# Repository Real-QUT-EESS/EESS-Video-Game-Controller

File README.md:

# EESS-Video-Game-Controller
A repository for the video game controller project from EESS

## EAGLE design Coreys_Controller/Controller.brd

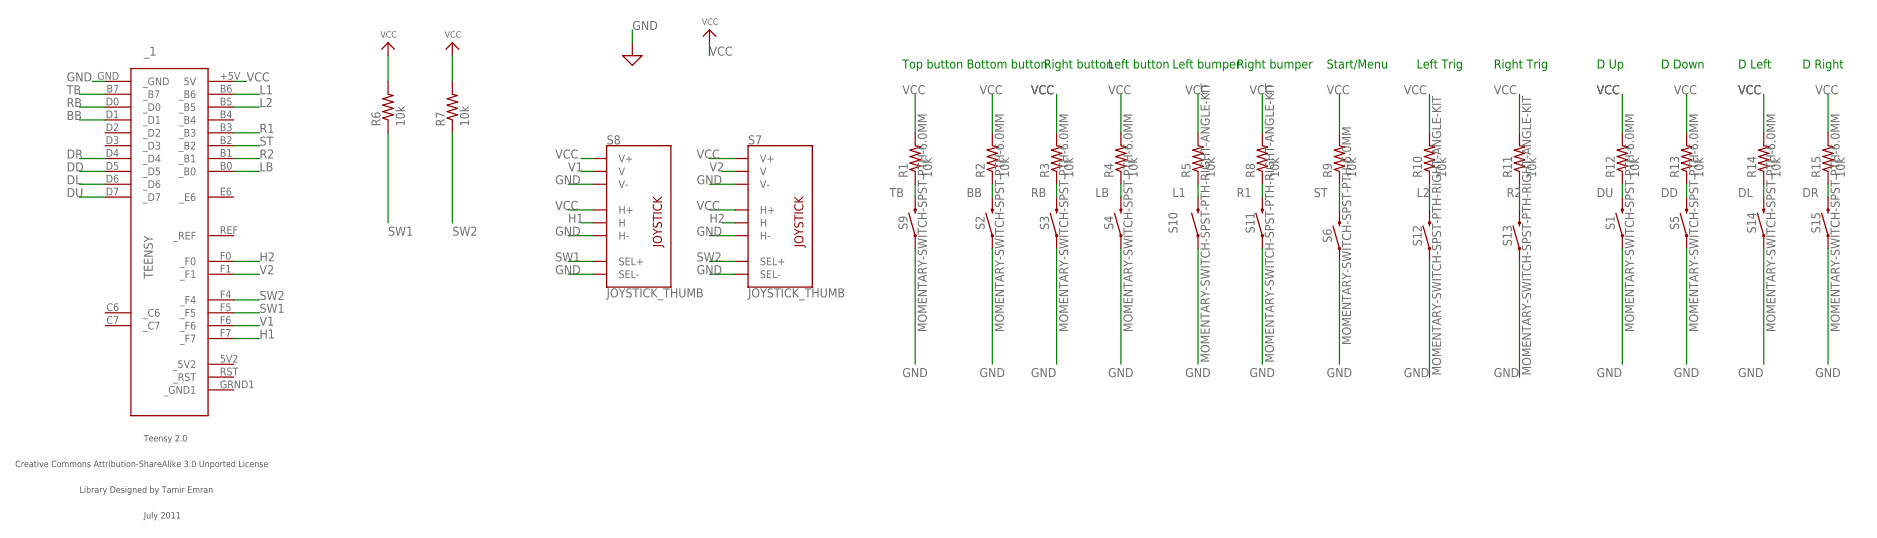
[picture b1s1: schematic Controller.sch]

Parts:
R1, R2, R3, R4, R5, R6, R7, R8, R9, R10, R11, R12, R13, R14, R15: 10k; 0207/10
S1, S2, S3, S4, S5, S6, S9, S14, S15: MOMENTARY-SWITCH-SPST-PTH-6.0MM; TACTILE_SWITCH_PTH_6.0MM
S7, S8: JOYSTICK_THUMB; JOYSTICK
S10, S11, S12, S13: MOMENTARY-SWITCH-SPST-PTH-RIGHT-ANGLE-KIT; TACTILE_SWITCH_PTH_RIGHT_ANGLE_KIT
_1: TEENSY

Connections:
BB: R2.1, S2.3 (2), _1.D1 (_D1)
DD: R13.1, S5.3 (2), _1.D5 (_D5)
DL: R14.1, S14.3 (2), _1.D6 (_D6)
DR: R15.1, S15.3 (2), _1.D4 (_D4)
DU: R12.1, S1.3 (2), _1.D7 (_D7)
GND: S1.1, S2.1, S3.1, S4.1, S5.1, S6.1, S7.B2A (SEL-), S7.H3 (H-), S7.V3 (V-), S8.B2A (SEL-), S8.H3 (H-), S8.V3 (V-), S9.1, S10.1, S11.1, S12.1, S13.1, S14.1, S15.1, _1.GND (_GND)
H1: S8.H2 (H), _1.F7 (_F7)
H2: S7.H2 (H), _1.F0 (_F0)
L1: R5.1, S10.2, _1.B6 (_B6)
L2: R10.1, S12.2, _1.B5 (_B5)
LB: R4.1, S4.3 (2), _1.B0 (_B0)
R1: R8.1, S11.2, _1.B3 (_B3)
R2: R11.1, S13.2, _1.B1 (_B1)
RB: R3.1, S3.3 (2), _1.D0 (_D0)
ST: R9.1, S6.3 (2), _1.B2 (_B2)
SW1: R6.1, S8.B1A (SEL+), _1.F5 (_F5)
SW2: R7.1, S7.B1A (SEL+), _1.F4 (_F4)
TB: R1.1, S9.3 (2), _1.B7 (_B7)
V1: S8.V2 (V), _1.F6 (_F6)
V2: S7.V2 (V), _1.F1 (_F1)
VCC: R1.2, R2.2, R3.2, R4.2, R5.2, R6.2, R7.2, R8.2, R9.2, R10.2, R11.2, R12.2, R13.2, R14.2, R15.2, S7.H1 (H+), S7.V1 (V+), S8.H1 (H+), S8.V1 (V+), _1.+5V (5V)

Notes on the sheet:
Top button
Bottom button
Right button
Left button
Left bumper
Right bumper
Start/Menu
Left Trig
Right Trig
D Up
D Down
D Left
D Right

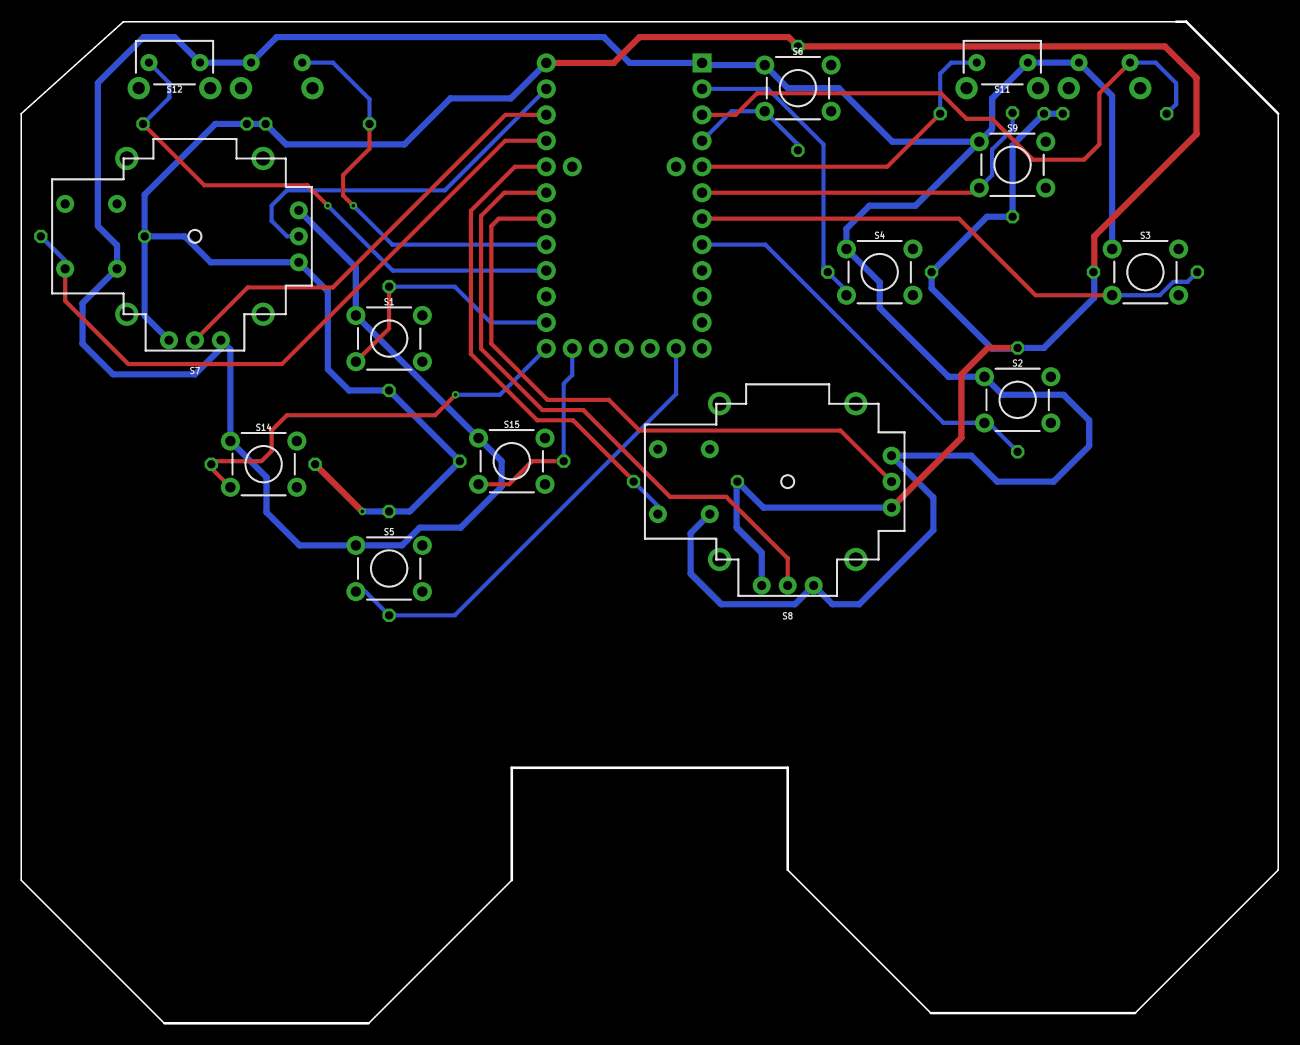
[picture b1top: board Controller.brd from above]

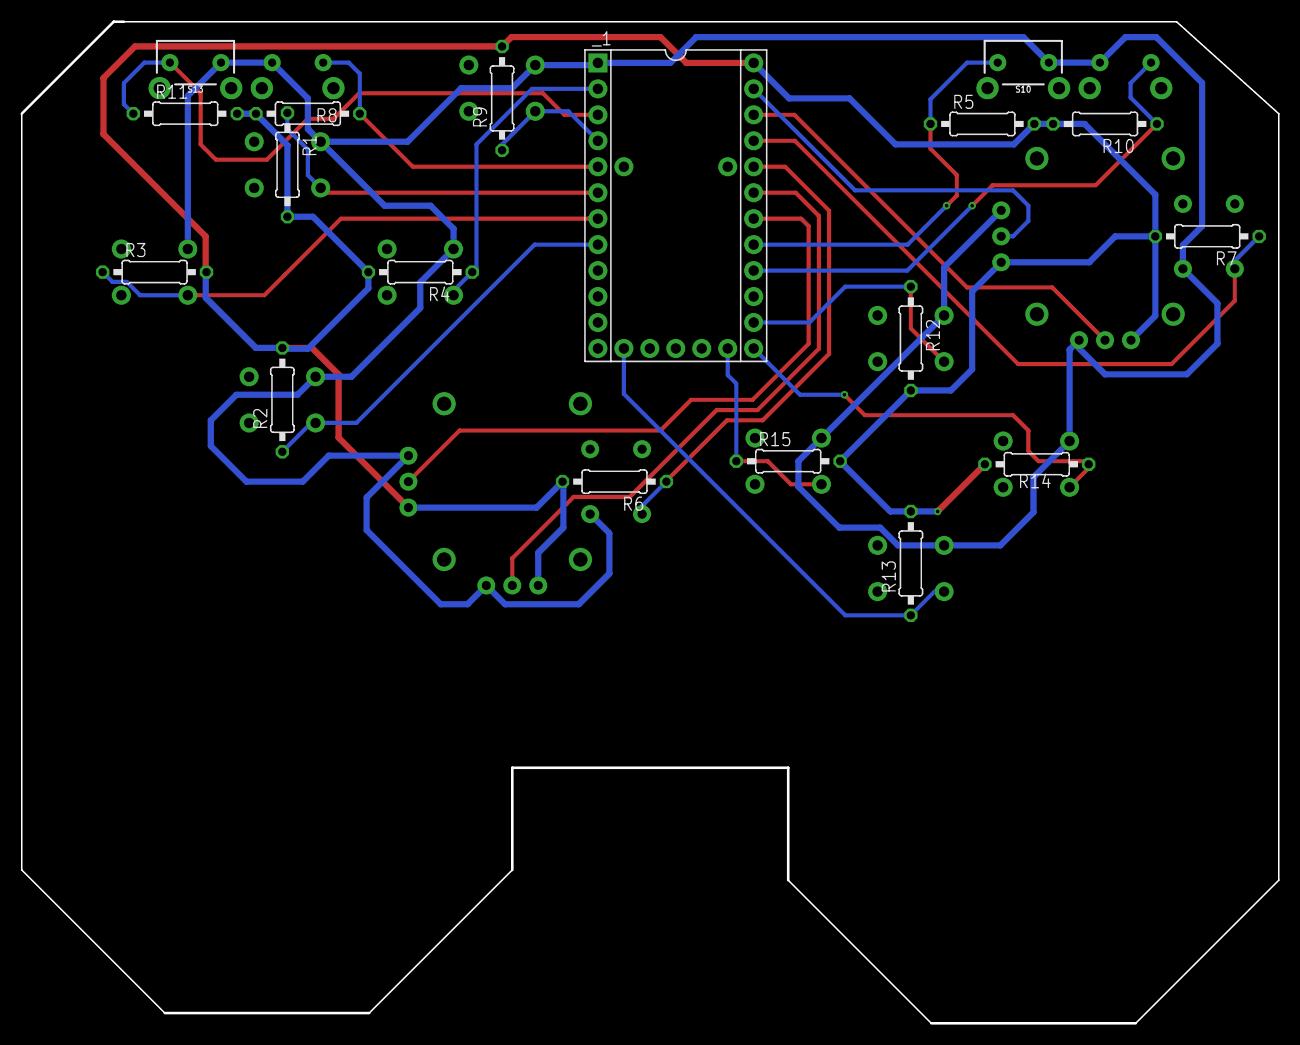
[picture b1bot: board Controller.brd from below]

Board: 2 copper layers, 123.0 x 98.0 mm, 31 parts (18 on the bottom side), 21 nets.

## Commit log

2022-07-17 test commit
2022-07-17 Added working controller for reference
2022-07-18 test update

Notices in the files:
parts and their libraries:
SparkFun-Switches: Licensing: Creative Commons ShareAlike 4.0 International - https://creativecommons.org/licenses/by-sa/4.0
teensy: Licensed Under Creative Commons
teensy: Creative Commons Attribution-ShareAlike 3.0 Unported License
